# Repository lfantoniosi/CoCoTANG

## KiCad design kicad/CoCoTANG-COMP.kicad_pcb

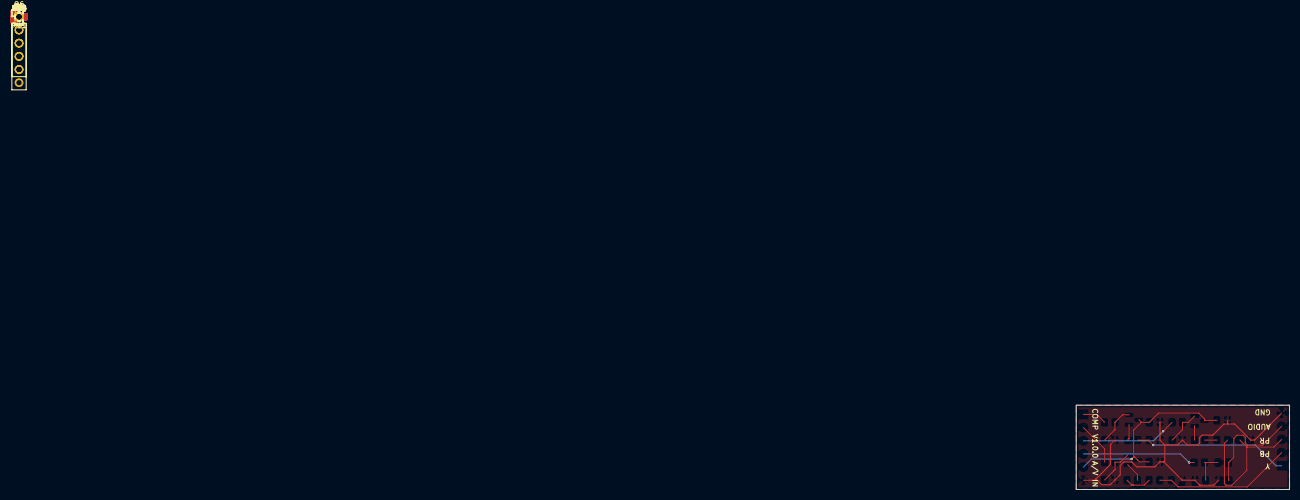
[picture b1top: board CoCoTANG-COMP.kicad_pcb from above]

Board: 2 copper layers, 41.1 x 16.3 mm, 26 parts (0 on the bottom side), 19 nets.

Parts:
C8, C9, C11: 470pF; C_0805_2012Metric_Pad1.18x1.45mm_HandSolder
C10, C12: 22uF; C_0805_2012Metric_Pad1.18x1.45mm_HandSolder
C24: 6.8nF; C_0805_2012Metric_Pad1.18x1.45mm_HandSolder
C25: 4.7uF; C_0805_2012Metric_Pad1.18x1.45mm_HandSolder
C29, C30, C31: 104; C_0805_2012Metric_Pad1.18x1.45mm_HandSolder
J18: CMP_IN; PinHeader_1x06_P2.54mm_Vertical
J21: CMP_OUT; PinHeader_1x05_P2.54mm_Vertical
Q4, Q5, Q6: MMBT3904; SOT-23
R10, R11, R12: 75; R_0805_2012Metric_Pad1.20x1.40mm_HandSolder
R23, R31, R33, R35: 1K; R_0805_2012Metric_Pad1.20x1.40mm_HandSolder
R24: 100K; R_0805_2012Metric_Pad1.20x1.40mm_HandSolder
R32, R34, R36: 4.7K; R_0805_2012Metric_Pad1.20x1.40mm_HandSolder

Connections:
+3.3V: C29.1, C30.1, C31.1, J18.5, Q4.3 (C), Q5.3 (C), Q6.3 (C)
AUDIO_33: J18.4, R23.1
AUDIO_RCA: C25.2, J21.4, R24.2
GND: C8.2, C9.2, C11.2, C24.1, C29.2, C30.2, C31.2, J18.6, J21.5, R24.1, R32.2, R34.2, R36.2
unnamed: C10.1, R11.2
unnamed: C12.1, R12.2
unnamed: C24.2, C25.1, R23.2
unnamed: Q4.1 (B), R31.2, R32.1
unnamed: Q4.2 (E), R10.1
unnamed: Q5.1 (B), R33.2, R34.1
unnamed: Q5.2 (E), R11.1
unnamed: Q6.1 (B), R35.2, R36.1
unnamed: Q6.2 (E), R12.1
PB_33: J18.2, R33.1
PB_RCA: C9.1, C10.2, J21.2
PR_33: J18.3, R35.1
PR_RCA: C11.1, C12.2, J21.3
Y_33: J18.1, R31.1
Y_RCA: C8.1, J21.1, R10.2

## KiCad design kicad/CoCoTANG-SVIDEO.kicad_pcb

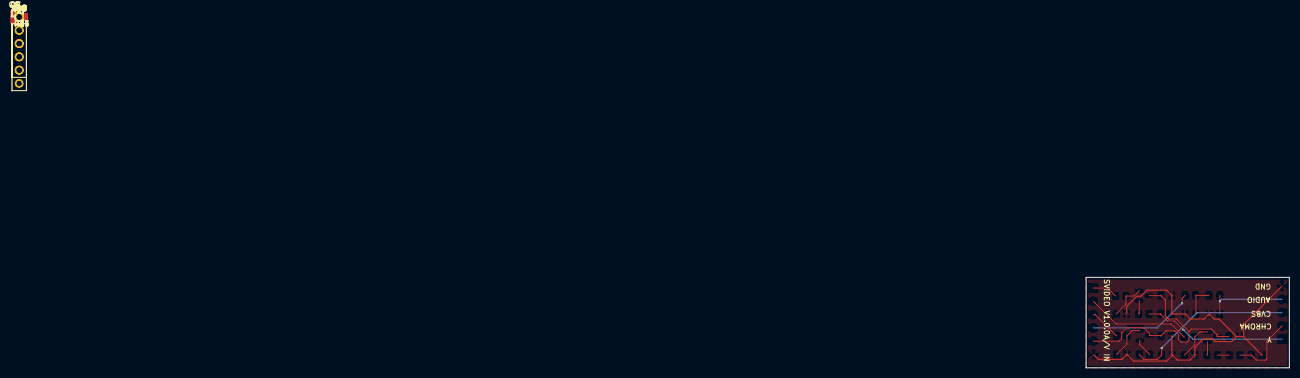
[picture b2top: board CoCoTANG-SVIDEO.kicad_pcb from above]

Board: 2 copper layers, 38.9 x 17.3 mm, 25 parts (0 on the bottom side), 18 nets.

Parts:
C13, C16: 470pF; C_0805_2012Metric_Pad1.18x1.45mm_HandSolder
C14: 680pF; C_0805_2012Metric_Pad1.18x1.45mm_HandSolder
C15: 1uF; C_0805_2012Metric_Pad1.18x1.45mm_HandSolder
C22: 6.8nF; C_0805_2012Metric_Pad1.18x1.45mm_HandSolder
C23: 4.7uF; C_0805_2012Metric_Pad1.18x1.45mm_HandSolder
C26, C27, C28: 104; C_0805_2012Metric_Pad1.18x1.45mm_HandSolder
J17: AV_IN; PinHeader_1x06_P2.54mm_Vertical
J20: AV_OUT; PinHeader_1x05_P2.54mm_Vertical
Q7, Q8, Q9: MMBT3904; SOT-23
R13, R14, R15: 75; R_0805_2012Metric_Pad1.20x1.40mm_HandSolder
R18, R25, R27, R29: 1K; R_0805_2012Metric_Pad1.20x1.40mm_HandSolder
R22: 100K; R_0805_2012Metric_Pad1.20x1.40mm_HandSolder
R26, R28, R30: 4.7K; R_0805_2012Metric_Pad1.20x1.40mm_HandSolder

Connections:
+3.3V: C26.1, C27.1, C28.1, J17.5, Q7.3 (C), Q8.3 (C), Q9.3 (C)
AUDIO_33: J17.4, R18.1
AUDIO_RCA: C23.2, J20.4, R22.2
CHROMA_33: J17.2, R27.1
CVBS_33: J17.3, R29.1
CVBS_RCA: C16.1, J20.3, R15.2
C_RCA: C14.1, C15.2, J20.2
GND: C13.2, C14.2, C16.2, C22.1, C26.2, C27.2, C28.2, J17.6, J20.5, R22.1, R26.2, R28.2, R30.2
unnamed: C15.1, R14.1
unnamed: C22.2, C23.1, R18.2
unnamed: Q7.1 (B), R25.2, R26.1
unnamed: Q7.2 (E), R13.2
unnamed: Q8.1 (B), R27.2, R28.1
unnamed: Q8.2 (E), R14.2
unnamed: Q9.1 (B), R29.2, R30.1
unnamed: Q9.2 (E), R15.1
Y_33: J17.1, R25.1
Y_RCA: C13.1, J20.1, R13.1
